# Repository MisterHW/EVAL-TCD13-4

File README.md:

# EVAL-TCD13-4
A 13 dB dual directional coupler designed with two Mini-Circuits TCD13-4+ for 5 to 1000 MHz.
Designed with KiCAD and tested in hardware.

## board view

The coupler is implemented using common Tg150 FR4 in 1.6 mm thickness and has four SMA edge ports.
50 Ohm traces are implemented as fenced stripline and tapered to connect to the transformer pads. 

the silkscreen showcases one of two 0° directional couplers, the kind which is detailed in [the excellent article by Michael G. Ellis](http://www.members.tripod.com/michaelgellis/direct.html)

## design

The design of the trace geometry to achieve 50 Ohm impedance was done using [atlc2](http://www.hdtvprimer.com/kq6qv/atlc2.html).
Via fencing may be a bit academic in this case but was implemented for educational purposes and because it is not reflected in the cost for the PCB.

## test results

One board was assembled and tested over 0.5 - 1800 MHz using an HP 4396B network analyzer. Coupling was found to be -12.6 dB at 900 MHz, with good flatness over the targeted frequency range.
Insertion loss and directivity are in agreement with typical values given in the [TCD13-4+](https://www.minicircuits.com/WebStore/dashboard.html?model=TCD-13-4%2B) characterization from Mini-Ciruits.

Here's what the assembled PCB looks like in action:

(Note: the PCB in the setup shows the wrong coupler circuit. This has been fixed in the project files. The rendering above depicts the correct circuit.)

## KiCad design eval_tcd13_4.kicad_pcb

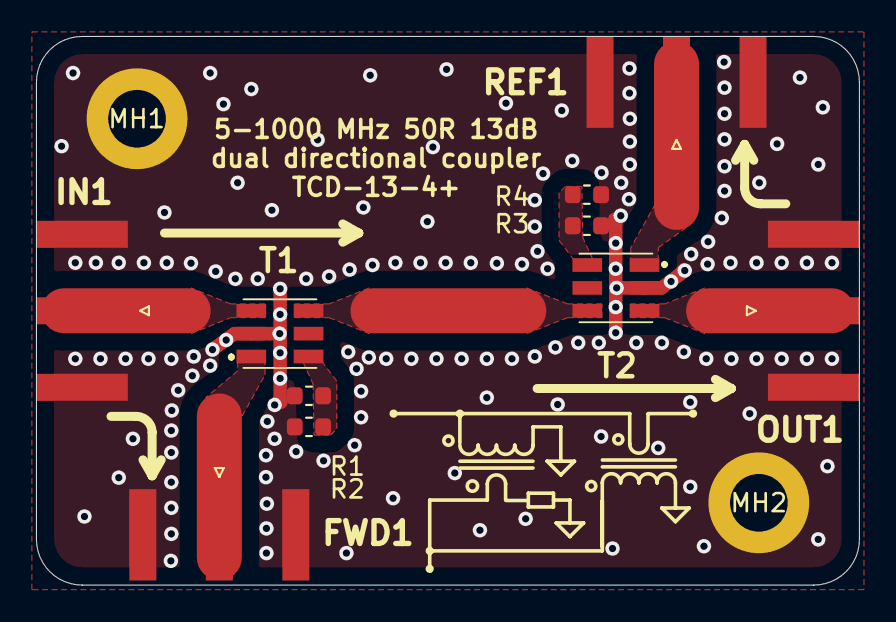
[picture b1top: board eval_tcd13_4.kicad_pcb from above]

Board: 2 copper layers, 45.7 x 30.5 mm, 12 parts (0 on the bottom side), 7 nets.

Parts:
FWD1: Conn_Coaxial; SMA_Amphenol_132289_EdgeMount
IN1: Conn_Coaxial; SMA_Amphenol_132289_EdgeMount
MH1, MH2: MountingHole_Pad; MountingHole_3.2mm_M3_DIN965_Pad
OUT1: Conn_Coaxial; SMA_Amphenol_132289_EdgeMount
R1, R2, R3, R4: 100; R_0603_1608Metric
REF1: Conn_Coaxial; SMA_Amphenol_132289_EdgeMount
T1, T2: TCD-13-4+; TCD134

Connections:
GND: FWD1.2, IN1.2, MH1.1, MH2.1, OUT1.2, R1.1, R2.1, R3.1, R4.1, REF1.2, T1.2, T2.2
unnamed: FWD1.1, T1.1
unnamed: IN1.1, T1.3
unnamed: OUT1.1, T2.3
unnamed: R1.2, R2.2, R3.2, R4.2, T1.6
unnamed: REF1.1, T2.1
unnamed: T1.4, T2.4

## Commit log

2019-03-10 repository created, initial commit with KiCAD project files and documentation.
2019-03-10 add image of the finished product
